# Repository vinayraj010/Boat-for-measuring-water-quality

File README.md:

# Boat-for-measuring-water-quality

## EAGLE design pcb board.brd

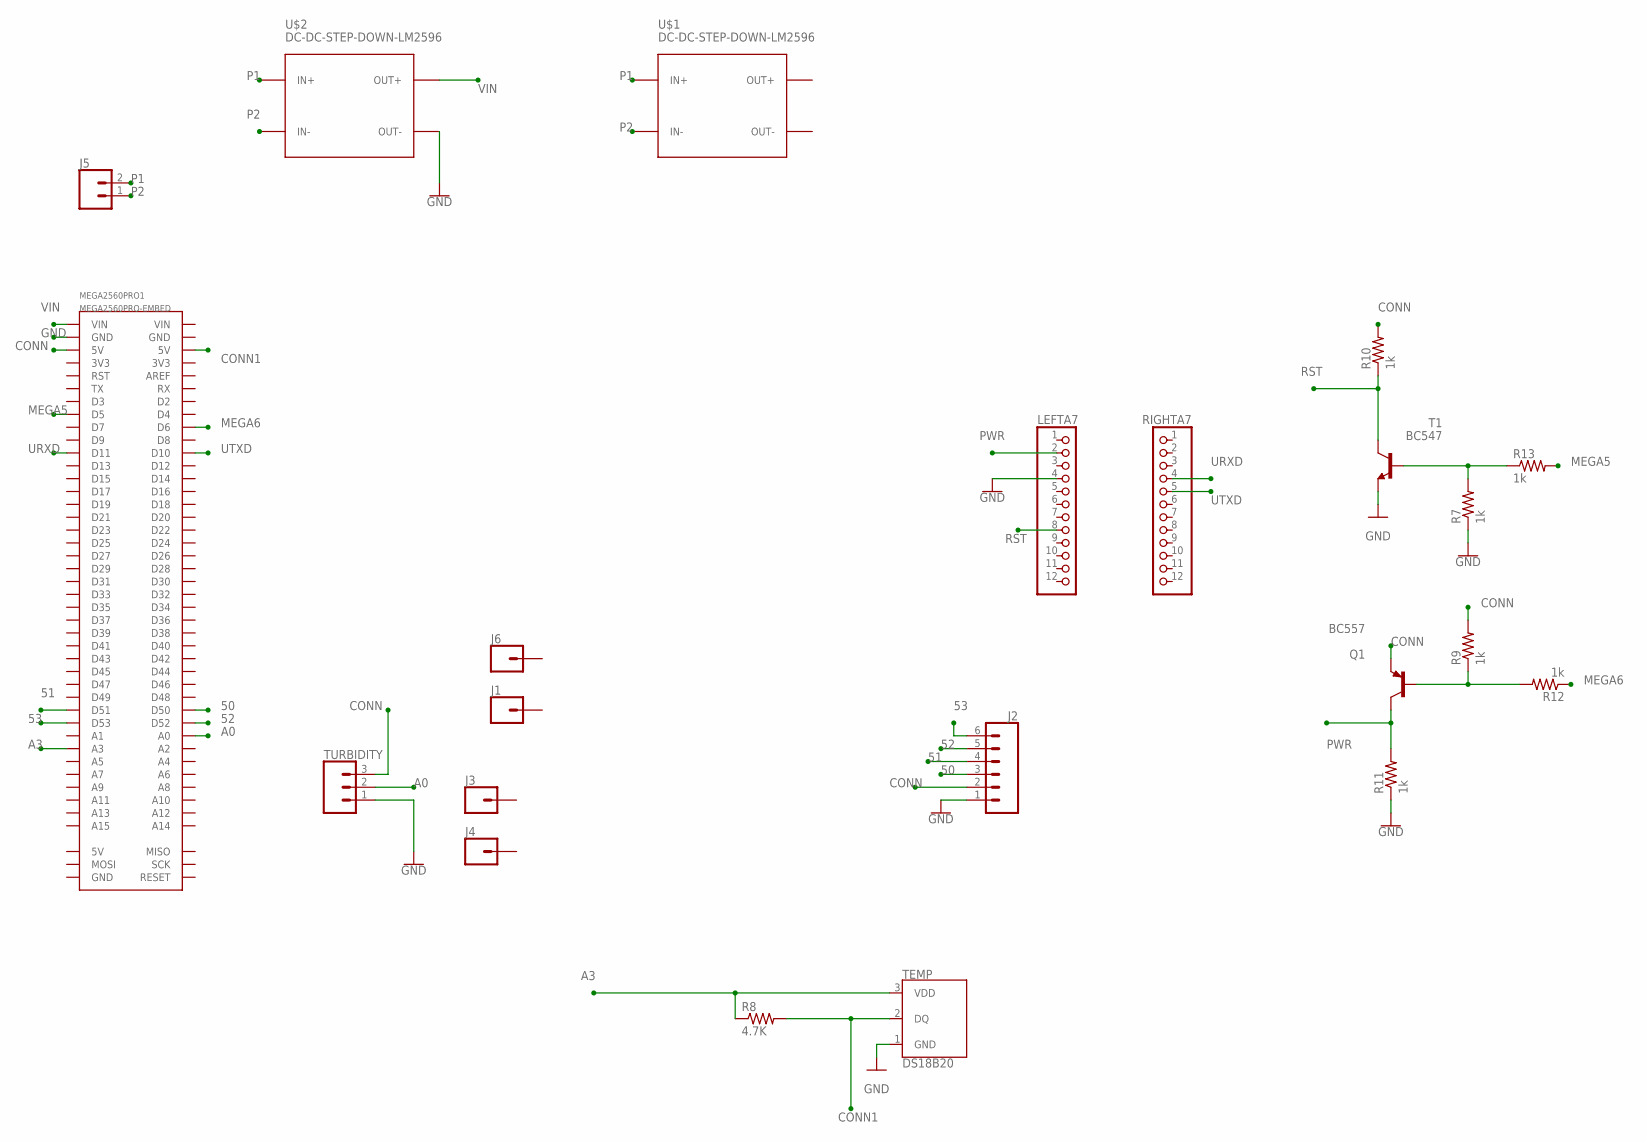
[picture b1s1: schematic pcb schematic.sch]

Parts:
J1, J3, J4, J6: CONN_01; 1X01
J2: CONN_06LOCK; 1X06_LOCK
J5: CONN_02; 1X02
LEFTA7: PINHD-1X12; 1X12
MEGA2560PRO1: MEGA2560PRO-EMBED
Q1: BC557; TO92-EBC
R7, R9, R10, R11, R12, R13: 1k; 0204/7
R8: 4.7K; 0204/7
RIGHTA7: PINHD-1X12; 1X12
T1: BC547; TO92
TEMP: DS18B20; TO-92-AMMO
TURBIDITY: 455-1750-1-ND; 1X03
U$1, U$2: DC-DC-STEP-DOWN-LM2596

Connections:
50: J2.3, MEGA2560PRO1.D50
51: J2.4, MEGA2560PRO1.D51
52: J2.5, MEGA2560PRO1.D52
53: J2.6, MEGA2560PRO1.D53
A0: MEGA2560PRO1.A0, TURBIDITY.2
A3: MEGA2560PRO1.A3, R8.1, TEMP.3 (VDD)
CONN: J2.2, MEGA2560PRO1.5V@1 (5V), Q1.E, R9.2, R10.2, TURBIDITY.3
CONN1: MEGA2560PRO1.5V@2 (5V), R8.2, TEMP.2 (DQ)
GND: J2.1, LEFTA7.4, MEGA2560PRO1.GND@1 (GND), R7.1, R11.1, T1.1 (E), TEMP.1 (GND), TURBIDITY.1, U$2.OUT-
MEGA5: MEGA2560PRO1.D5, R13.2
MEGA6: MEGA2560PRO1.D6, R12.1
unnamed: Q1.B, R9.1, R12.2
unnamed: R7.2, R13.1, T1.2 (B)
P1: J5.2, U$1.IN+, U$2.IN+
P2: J5.1, U$1.IN-, U$2.IN-
PWR: LEFTA7.2, Q1.C, R11.2
RST: LEFTA7.8, R10.1, T1.3 (C)
URXD: MEGA2560PRO1.D11, RIGHTA7.4
UTXD: MEGA2560PRO1.D10, RIGHTA7.5
VIN: MEGA2560PRO1.VIN@1 (VIN), U$2.OUT+

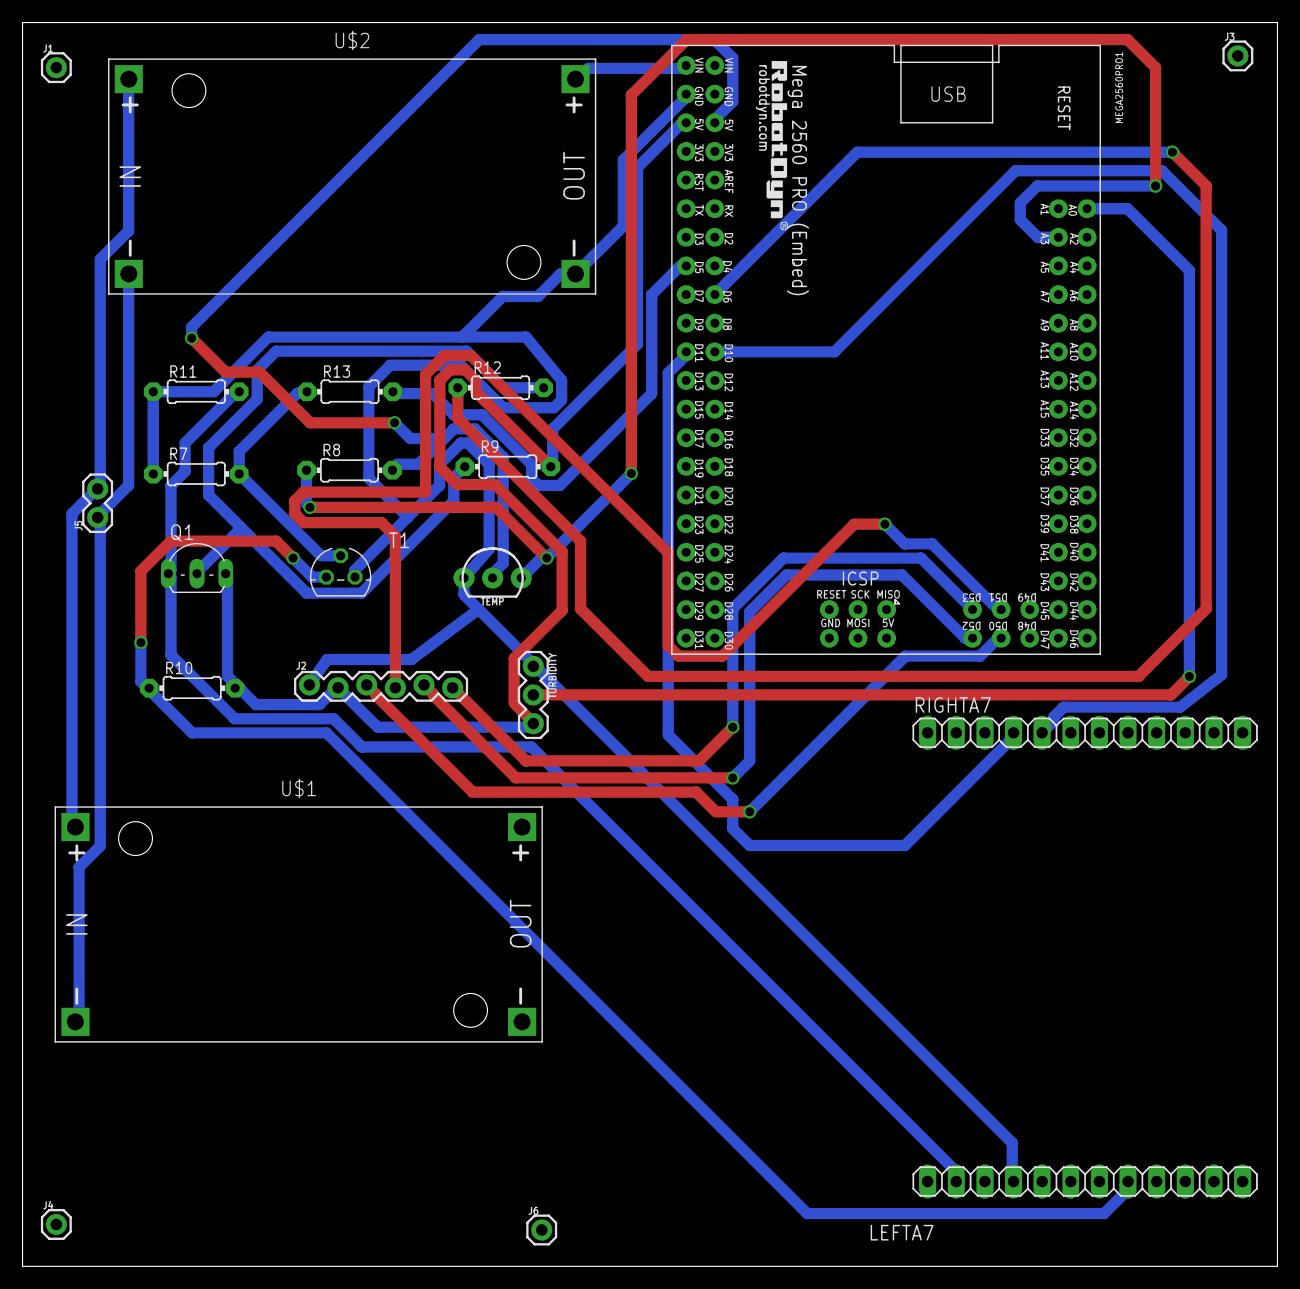
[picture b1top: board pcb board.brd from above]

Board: 2 copper layers, 111.3 x 110.3 mm, 22 parts (0 on the bottom side), 20 nets.

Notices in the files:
parts and their libraries:
SparkFun-Connectors: Licensing: Creative Commons ShareAlike 4.0 International - https://creativecommons.org/licenses/by-sa/4.0
diy-modules: Released under the Creative Commons Attribution 4.0 International License: http://creativecommons.org/licenses/by/4.0
